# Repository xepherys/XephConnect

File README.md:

# XephConnect
Daughter Board / Breakout Board for moving Duet connections to the tool.

This PCB design is being created for the RailCore II to move carriage-based connections (extruder steppers, thermistor, heater, Y-stop) to the tool using a single wire harness.

The idea for this started with my desire to create a tool carriage for the M3D QuadFusion, which has four (4) extruder steppers, but being able to run a single connector up to the tool that can swap between the QuadFusion and the E3D standard hotends.

In current iterations, the design calls for a TE 32-pin connector.  See PARTLIST.txt in the individual version folder for information on the components required.  See VERNOTES.txt for information and notes on each version.

v0.1 was the original design.  I hadn't designed a PCB in quite some time, and used auto-router. Not the greatest plan.  It's functional (it's on my RailCore II 300ZL currently, as of 7/4/19), but it has some issues with noise from the steppers interfering with the z-probe, and a few issues with hole spacing (one of the screws doesn't play nicely with one of the Molex headers).

v0.6, as of this update (7/4/19) is being manufactured as a prototype.  I should be testing it as soon as it arrives.  It requires different wiring of the main wire harness, but also includes wiring for the heater cartridge.

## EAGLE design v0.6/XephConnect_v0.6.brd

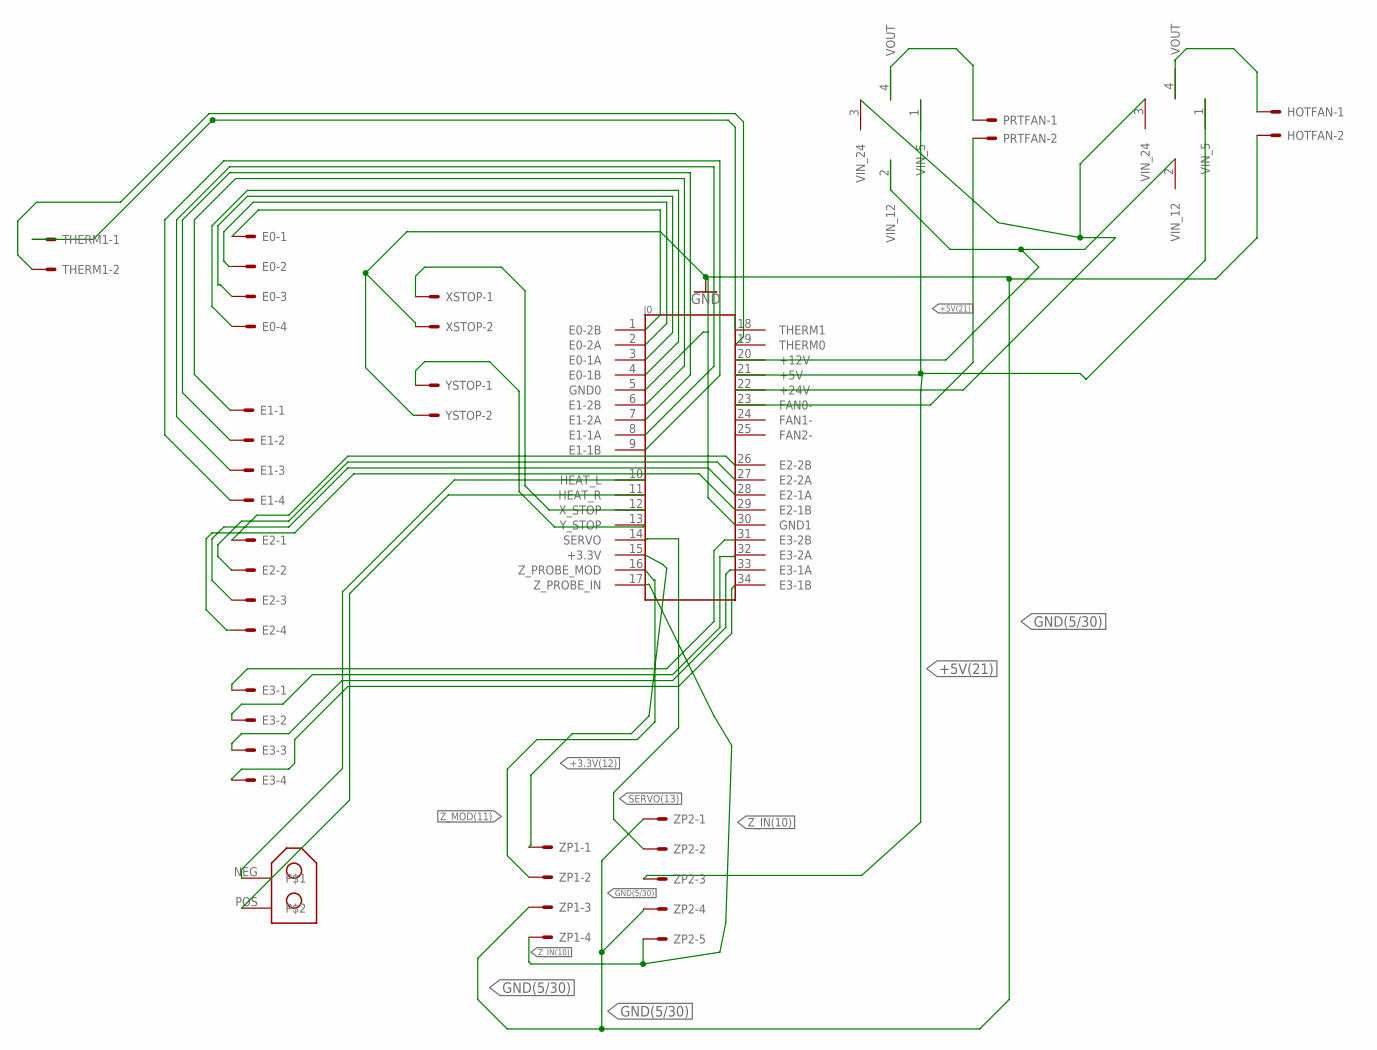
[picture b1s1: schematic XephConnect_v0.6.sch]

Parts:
E0, E1, E2, E3: 22-27-2041-04; 6410-04
HOTFAN: 22-27-2021-02; 6410-02
J0: 6437288-1-V2; TE_6437288-1
PRTFAN: 22-27-2021-02; 6410-02
THERM1: 22-27-2021-02; 6410-02
U$1, U$2: CONN_03+01(T)(SM); 1X03X01(SM)
U$3: XT30; XT30-90
XSTOP: 22-27-2021-02; 6410-02
YSTOP: 22-27-2021-02; 6410-02
ZP1: 22-27-2041-04; 6410-04
ZP2: 22-27-2051-05; 6410-05

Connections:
+3.3V(12): J0.15 (+3.3V), ZP1.1
+5V(21): J0.21 (+5V), U$1.1 (VIN_5), U$2.1 (VIN_5), ZP2.3
+12V(20): J0.20 (+12V), U$1.2 (VIN_12), U$2.2 (VIN_12)
+24V(22): J0.22 (+24V), U$1.3 (VIN_24), U$2.3 (VIN_24)
E0-1A: E0.3, J0.3 (E0-1A)
E0-1B: E0.4, J0.4 (E0-1B)
E0-2A: E0.2, J0.2 (E0-2A)
E0-2B: E0.1, J0.1 (E0-2B)
E1-1A: E1.3, J0.8 (E1-1A)
E1-1B: E1.4, J0.9 (E1-1B)
E1-2A: E1.2, J0.7 (E1-2A)
E1-2B: E1.1, J0.6 (E1-2B)
E2-1A: E2.3, J0.28 (E2-1A)
E2-1B: E2.4, J0.29 (E2-1B)
E2-2A: E2.2, J0.27 (E2-2A)
E2-2B: E2.1, J0.26 (E2-2B)
E3-1A: E3.3, J0.33 (E3-1A)
E3-1B: E3.4, J0.34 (E3-1B)
E3-2A: E3.2, J0.32 (E3-2A)
E3-2B: E3.1, J0.31 (E3-2B)
FAN0-(23): J0.23 (FAN0-), PRTFAN.2
FAN1-: J0.24 (FAN1-)
FAN2-: J0.25 (FAN2-)
GND(5/30): HOTFAN.2, J0.5 (GND0), J0.30 (GND1), XSTOP.2, YSTOP.2, ZP1.3, ZP2.1, ZP2.4
HEAT0: J0.10 (HEAT_L), U$3.NEG
HEAT1: J0.11 (HEAT_R), U$3.POS
unnamed: HOTFAN.1, U$2.4 (VOUT)
unnamed: PRTFAN.1, U$1.4 (VOUT)
SERVO(13): J0.14 (SERVO), ZP2.2
THERM0: J0.18 (THERM1), THERM1.1
THERM1: J0.19 (THERM0), THERM1.2
X_STOP: J0.12 (X_STOP), XSTOP.1
Y_STOP: J0.13 (Y_STOP), YSTOP.1
Z_IN(10): J0.17 (Z_PROBE_IN), ZP1.4, ZP2.5
Z_MOD(11): J0.16 (Z_PROBE_MOD), ZP1.2

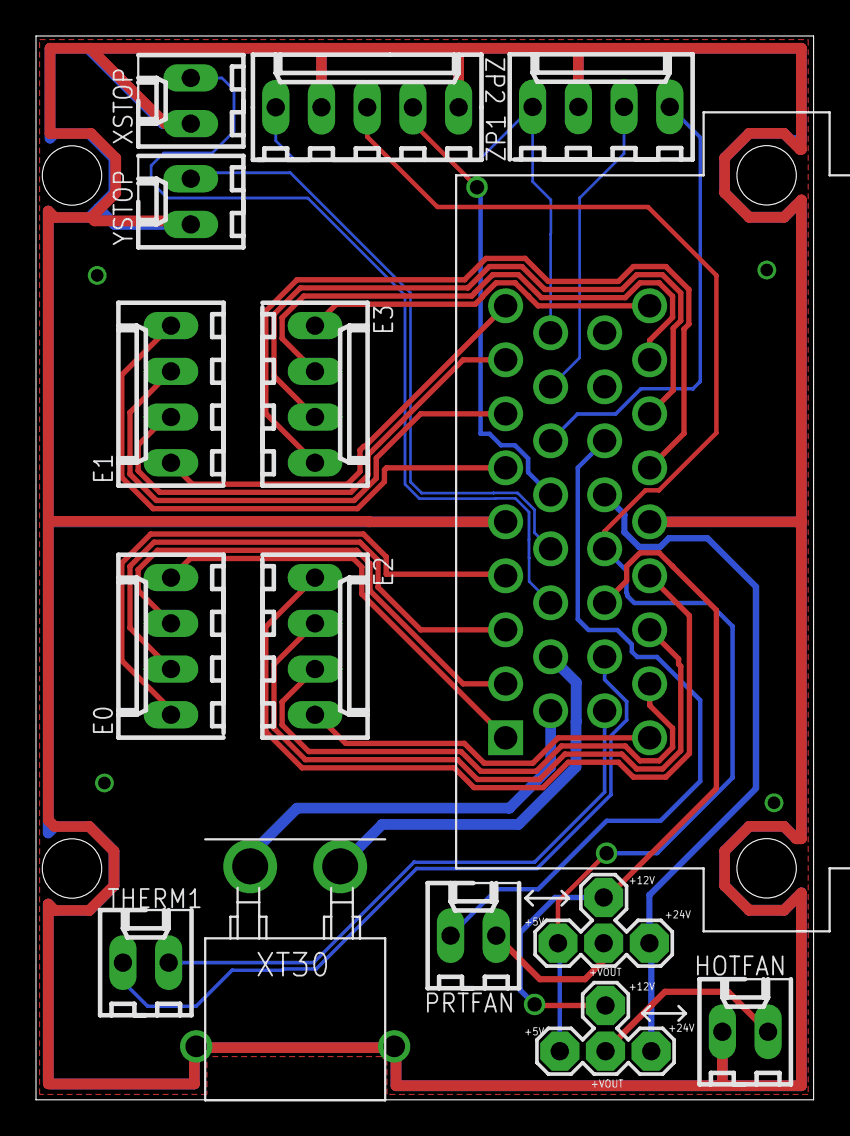
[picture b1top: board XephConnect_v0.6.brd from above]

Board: 2 copper layers, 43.2 x 59.1 mm, 15 parts (0 on the bottom side), 33 nets.

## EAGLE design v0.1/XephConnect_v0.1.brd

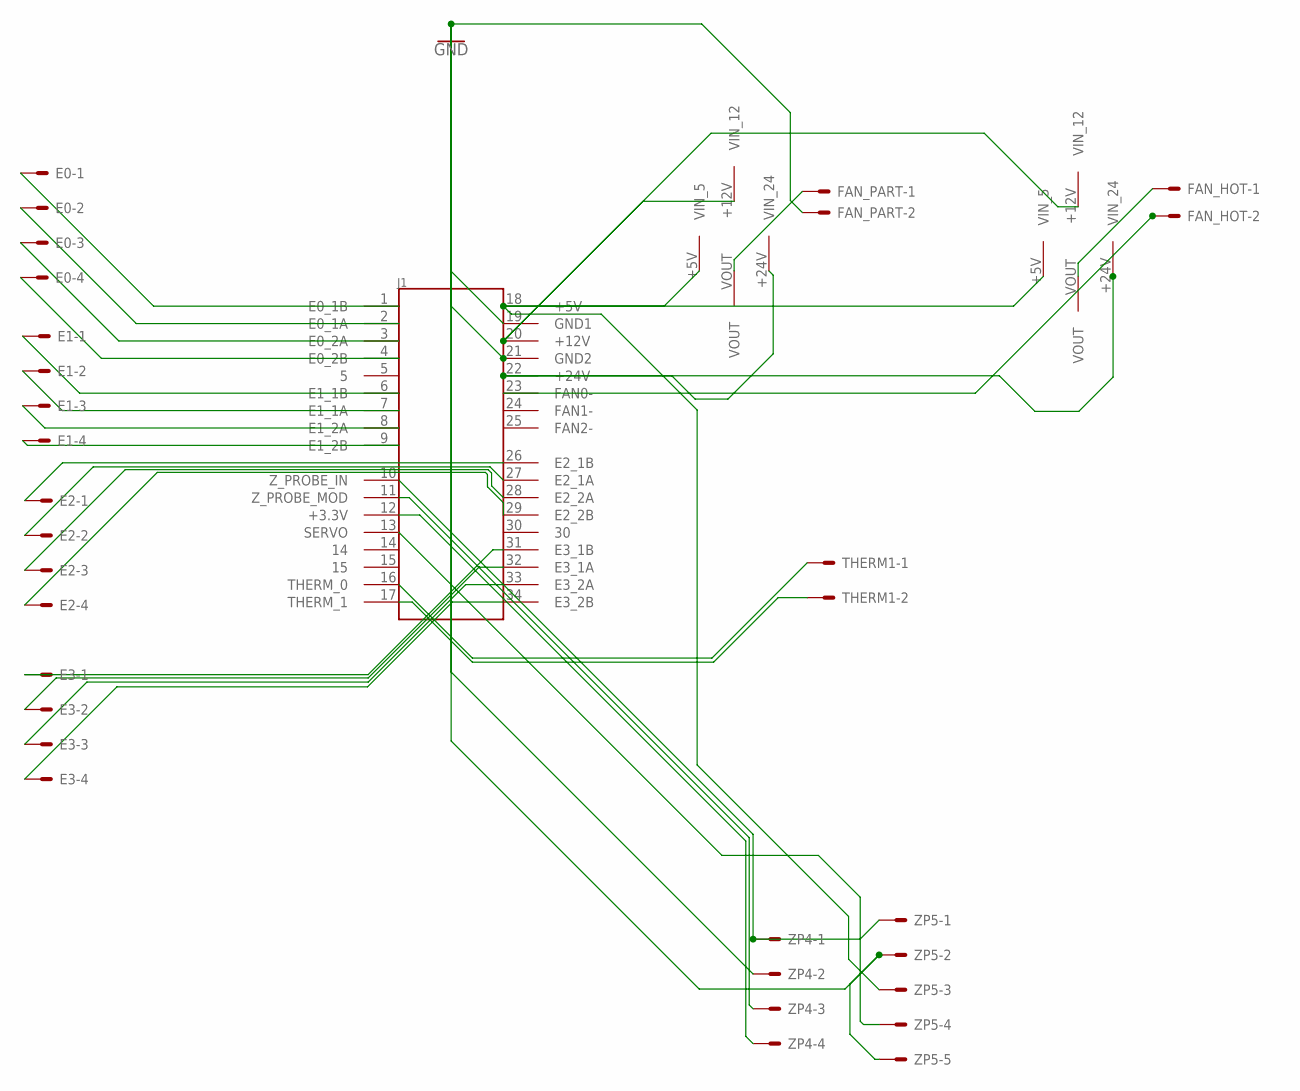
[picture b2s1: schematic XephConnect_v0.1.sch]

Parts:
E0, E1, E2, E3: 22-27-2041-04; 6410-04
FAN_HOT: 22-27-2021-02; 6410-02
FAN_PART: 22-27-2021-02; 6410-02
J1: 6437288-1; TE_6437288-1
THERM1: 22-27-2021-02; 6410-02
U$1, U$2: CONN_03+01(T); 1X03X01
ZP4: 22-27-2041-04; 6410-04
ZP5: 22-27-2051-05; 6410-05

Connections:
FAN1-: J1.24 (FAN1-)
FAN2-: J1.25 (FAN2-)
GND: FAN_PART.2, J1.19 (GND1), J1.21 (GND2), ZP4.2, ZP5.2, ZP5.5
unnamed: E0.1, J1.1 (E0_1B)
unnamed: E0.2, J1.2 (E0_1A)
unnamed: E0.3, J1.3 (E0_2A)
unnamed: E0.4, J1.4 (E0_2B)
unnamed: J1.10 (Z_PROBE_IN), ZP4.1, ZP5.1
unnamed: E1.1, J1.6 (E1_1B)
unnamed: E1.2, J1.7 (E1_1A)
unnamed: E1.3, J1.8 (E1_2A)
unnamed: E1.4, J1.9 (E1_2B)
unnamed: E2.1, J1.26 (E2_1B)
unnamed: E2.2, J1.27 (E2_1A)
unnamed: E2.3, J1.28 (E2_2A)
unnamed: E2.4, J1.29 (E2_2B)
unnamed: E3.1, J1.31 (E3_1B)
unnamed: E3.2, J1.32 (E3_1A)
unnamed: E3.3, J1.33 (E3_2A)
unnamed: E3.4, J1.34 (E3_2B)
unnamed: J1.16 (THERM_0), THERM1.1
unnamed: J1.17 (THERM_1), THERM1.2
unnamed: J1.18 (+5V), U$1.+5V (VIN_5), U$2.+5V (VIN_5), ZP5.3
unnamed: J1.20 (+12V), U$1.+12V (VIN_12), U$2.+12V (VIN_12)
unnamed: FAN_HOT.2, J1.23 (FAN0-)
unnamed: J1.22 (+24V), U$1.+24V (VIN_24), U$2.+24V (VIN_24)
unnamed: FAN_PART.1, U$1.VOUT
unnamed: FAN_HOT.1, U$2.VOUT
unnamed: J1.11 (Z_PROBE_MOD), ZP4.3
unnamed: J1.12 (+3.3V), ZP4.4
unnamed: J1.13 (SERVO), ZP5.4

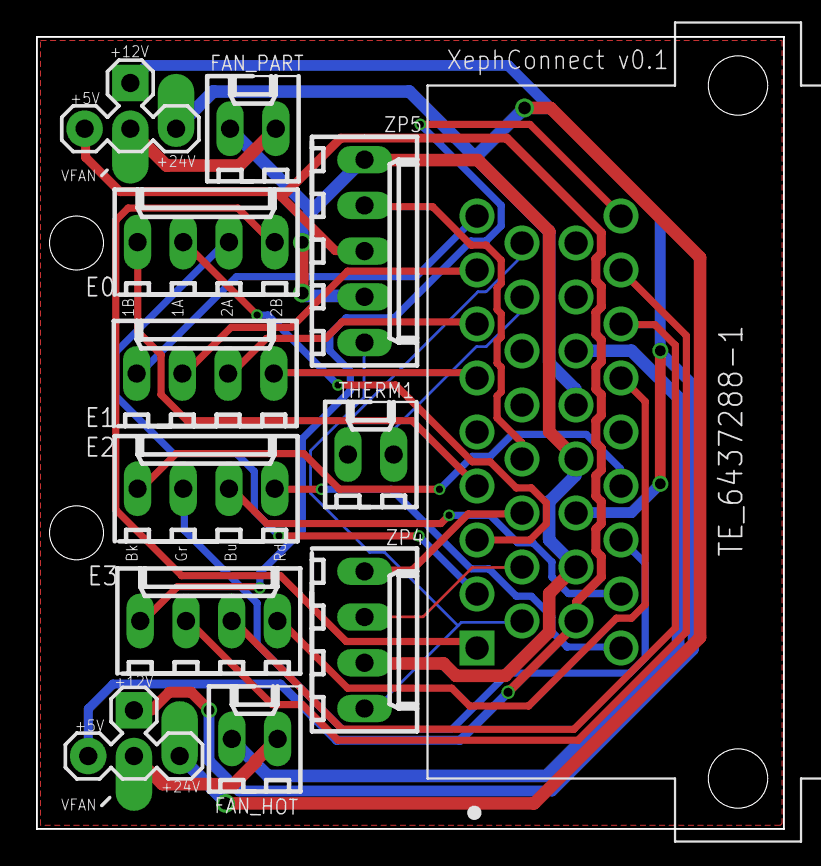
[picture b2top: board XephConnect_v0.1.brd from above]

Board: 2 copper layers, 41.5 x 44.0 mm, 12 parts (0 on the bottom side), 29 nets.

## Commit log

2019-07-04 Upload of v0.1 and v0.6 designs
    Eagle .brd/.sch uploads and CAM outputs (Gerber + Drill) for v0.1 and v0.6 of the XephConnect board.
2019-07-04 Update v0.1 to have ground plane
2019-07-04 Added 'ISSUES'
2019-07-04 Update issue templates
2019-07-04 Set theme jekyll-theme-midnight
2019-07-04 Set theme jekyll-theme-modernist

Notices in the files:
parts and their libraries:
SparkFun-PowerSymbols: Licensing: Creative Commons ShareAlike 4.0 International - https://creativecommons.org/licenses/by-sa/4.0
